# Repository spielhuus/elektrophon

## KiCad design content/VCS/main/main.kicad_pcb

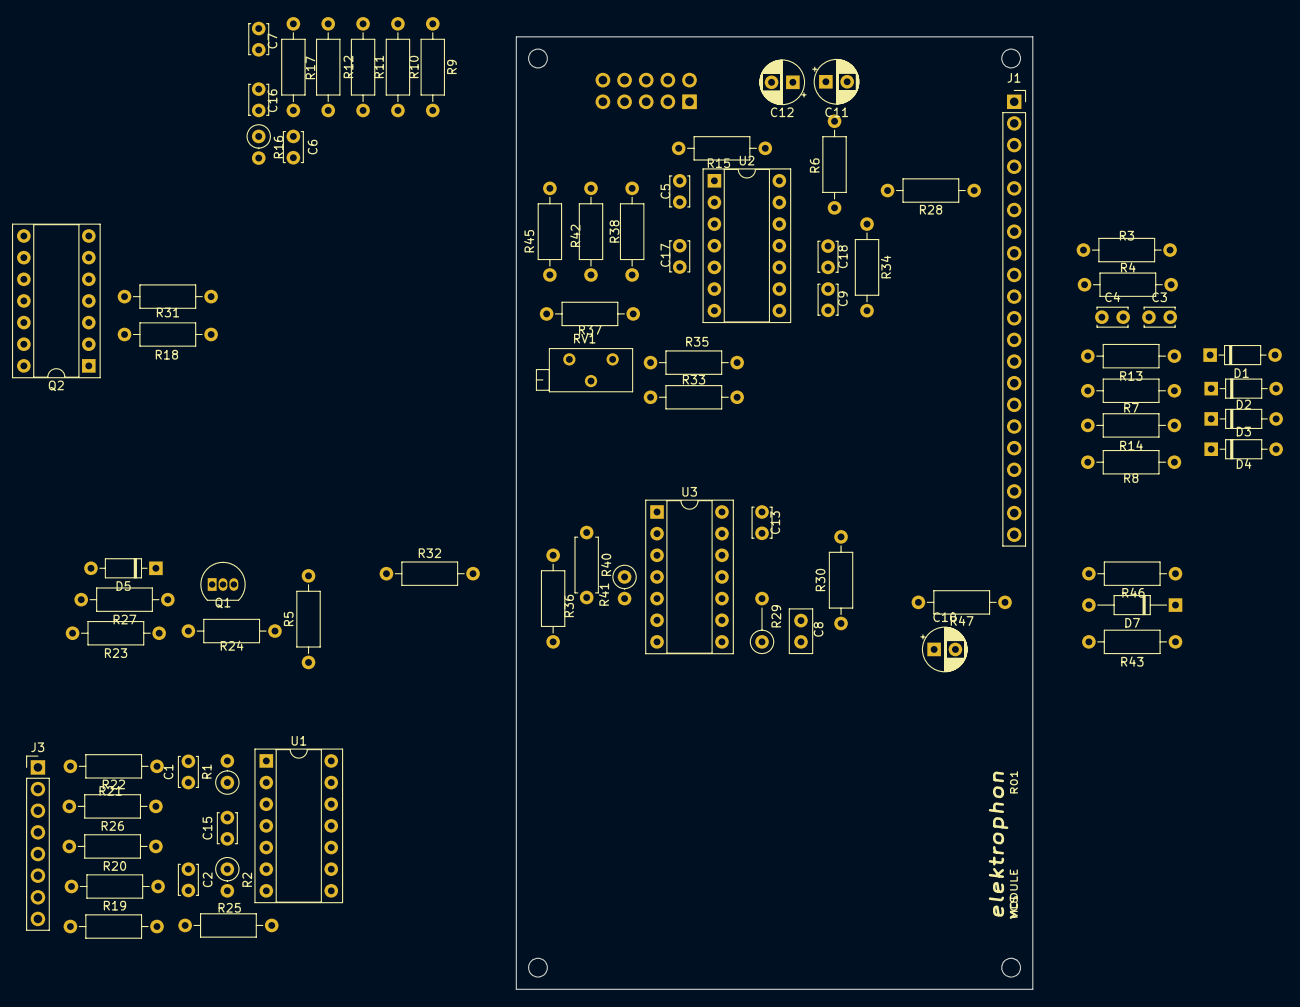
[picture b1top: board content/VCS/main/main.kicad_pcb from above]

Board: 2 copper layers, 60.6 x 111.8 mm, 81 parts (1 on the bottom side), 55 nets, no tracks yet.

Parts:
C1, C2, C5, C6, C7: 47p; C_Disc_D3.4mm_W2.1mm_P2.50mm
C3, C4: 1n; C_Disc_D3.4mm_W2.1mm_P2.50mm
C8: 47p; C_Disc_D5.0mm_W2.5mm_P2.50mm
C9: 22n; C_Disc_D3.4mm_W2.1mm_P2.50mm
C10: 47u; CP_Radial_D5.0mm_P2.50mm
C11, C12: 10u; CP_Radial_D5.0mm_P2.50mm
C13, C15, C16, C17, C18: 0.1u; C_Disc_D3.4mm_W2.1mm_P2.50mm
D1, D2, D3, D4, D5: 1N4148; D_DO-35_SOD27_P7.62mm_Horizontal
D7: 5v5; D_DO-35_SOD27_P10.16mm_Horizontal
H1, H2, H3, H4: MountingHole; MountingHole_2.2mm_M2
J1: Conn_01x21_Female; PinSocket_1x21_P2.54mm_Vertical
J2: IDC Header; IDC-Header_2x05_P2.54mm_Vertical
J3: Conn_01x08_Female; PinHeader_1x08_P2.54mm_Vertical
Q1: 2N3906; TO-92_Inline
Q2: THAT340; DIP-14_W7.62mm_Socket
R1, R2: 100k; R_Axial_DIN0207_L6.3mm_D2.5mm_P2.54mm_Vertical
R3, R4, R5, R6, R7, R8, R37, R42: 100k; R_Axial_DIN0207_L6.3mm_D2.5mm_P10.16mm_Horizontal
R9, R11, R47: 1M; R_Axial_DIN0207_L6.3mm_D2.5mm_P10.16mm_Horizontal
R10, R12: 470k; R_Axial_DIN0207_L6.3mm_D2.5mm_P10.16mm_Horizontal
R13, R14: 33k; R_Axial_DIN0207_L6.3mm_D2.5mm_P10.16mm_Horizontal
R15: 10M; R_Axial_DIN0207_L6.3mm_D2.5mm_P10.16mm_Horizontal
R16: 820k; R_Axial_DIN0207_L6.3mm_D2.5mm_P2.54mm_Vertical
R17, R30: 820k; R_Axial_DIN0207_L6.3mm_D2.5mm_P10.16mm_Horizontal
R18: 8k2; R_Axial_DIN0207_L6.3mm_D2.5mm_P10.16mm_Horizontal
R19, R20, R21, R22, R28: 82k; R_Axial_DIN0207_L6.3mm_D2.5mm_P10.16mm_Horizontal
R23, R27, R32, R33: 220k; R_Axial_DIN0207_L6.3mm_D2.5mm_P10.16mm_Horizontal
R24: 68k; R_Axial_DIN0207_L6.3mm_D2.5mm_P10.16mm_Horizontal
R25, R26, R43: 2k2; R_Axial_DIN0207_L6.3mm_D2.5mm_P10.16mm_Horizontal
R29: 820k; R_Axial_DIN0207_L6.3mm_D2.5mm_P5.08mm_Vertical
R31: 1k8; R_Axial_DIN0207_L6.3mm_D2.5mm_P10.16mm_Horizontal
R34: 100; R_Axial_DIN0207_L6.3mm_D2.5mm_P10.16mm_Horizontal
R35: 330k; R_Axial_DIN0207_L6.3mm_D2.5mm_P10.16mm_Horizontal
R36: 10m; R_Axial_DIN0207_L6.3mm_D2.5mm_P10.16mm_Horizontal
R38: 620k; R_Axial_DIN0207_L6.3mm_D2.5mm_P10.16mm_Horizontal
R40: 1m; R_Axial_DIN0207_L6.3mm_D2.5mm_P7.62mm_Horizontal
R41: 1m; R_Axial_DIN0207_L6.3mm_D2.5mm_P2.54mm_Vertical
R45: 330; R_Axial_DIN0207_L6.3mm_D2.5mm_P10.16mm_Horizontal
R46: 1k; R_Axial_DIN0207_L6.3mm_D2.5mm_P10.16mm_Horizontal
RV1: 100k; Potentiometer_Bourns_3296Z_Horizontal
U1, U2: TL074; DIP-14_W7.62mm_Socket
U3: LM3900; DIP-14_W7.62mm_Socket

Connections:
+5V: J2.9, J2.10
+15V: C11.1, C13.1, C13.2, C15.1, C15.2, C16.1, C17.1, C17.2, C18.1, J1.2, J2.3, J2.4, Q1.1, R24.1, R36.1, U1.4, U2.4, U3.7, U3.14
-15V: C12.2, C16.2, C18.2, J1.3, J2.1, J2.2, R27.2, U1.11, U2.11
/AC_OUT: C10.2, J1.9, R47.1
/BIPOLAR_OUT: J1.6, R42.2, R45.2
/CV: J1.5, R28.1
/CYCLE_1: C4.2, J1.11, R4.2
/CYCLE_2: D2.1, D4.1, J1.10, R46.1
/FALL: C1.1, J3.5, R1.1, U1.2
/FALL_1: C1.2, J3.4, R1.2, R10.1, U1.1
/FALL_2: J3.6, U1.10
/FALL_RATE: J3.7, R20.1
/IN: J1.4, R5.2, R6.1
/NET_1: C9.2, J1.7, R32.2, R34.1, U2.8
/OUT: C10.1, J1.8, R34.2, R35.2, R37.1, RV1.3
/RISE: C2.1, J3.8, R2.1, U1.6
/RISE_1: C2.2, J3.3, R2.2, R12.1, U1.7
/RISE_2: J3.2, U1.12
/RISE_RATE: J3.1, R22.1
/TRIGGER: C3.2, J1.12, R3.2
GND: C11.2, C12.1, D7.2, J1.1, J2.5, J2.6, J2.7, J2.8, Q2.1, Q2.4, Q2.7, Q2.11, R3.1, R4.1, R5.1, R7.1, R8.1, R9.1, R11.1, R25.2, R26.2, R31.2, R38.1, R47.2, RV1.1, U1.3, U1.5, U2.5, U2.10, U2.12, U3.1
unnamed: C3.1, R7.2, R13.1
unnamed: C4.1, R8.2, R14.1
unnamed: C5.1, R15.1
unnamed: C5.2, R6.2, U2.2
unnamed: C6.1, R9.2, R10.2, R16.1, U1.9
unnamed: C6.2, R16.2, R19.1, U1.8
unnamed: C7.1, R11.2, R12.2, R17.1, U1.13
unnamed: C7.2, R17.2, R21.1, U1.14
unnamed: C8.1, R29.1, U3.8
unnamed: C8.2, R29.2, U3.10
unnamed: C9.1, Q2.8, Q2.14, U2.9
unnamed: D1.1, D3.1, U3.13
unnamed: D1.2, D2.2, R13.2
unnamed: D3.2, D4.2, R14.2
unnamed: D5.1, Q1.3, R27.1
unnamed: D5.2, R32.1, U2.3
unnamed: D7.1, R43.1, R46.2
unnamed: Q1.2, R23.2, R24.2
unnamed: Q2.2, R21.2, R22.2, R26.1
unnamed: Q2.9, R19.2, R20.2, R25.1
unnamed: Q2.3, Q2.5, Q2.10, Q2.12, R18.2
unnamed: Q2.6, Q2.13, R28.2, R31.1
unnamed: R15.2, R18.1, U2.1
unnamed: R30.2, U3.11
unnamed: R33.1, U3.12
unnamed: R33.2, RV1.2
unnamed: R35.1, R36.2, U3.3
unnamed: R37.2, R38.2, R42.1, U2.6
unnamed: R40.1, R41.1, R43.2, U3.4
unnamed: R40.2, U3.2
unnamed: R41.2, U3.6
unnamed: R45.1, U2.7
unnamed: U2.13, U2.14
TRIG: R23.1, R30.1, U3.9

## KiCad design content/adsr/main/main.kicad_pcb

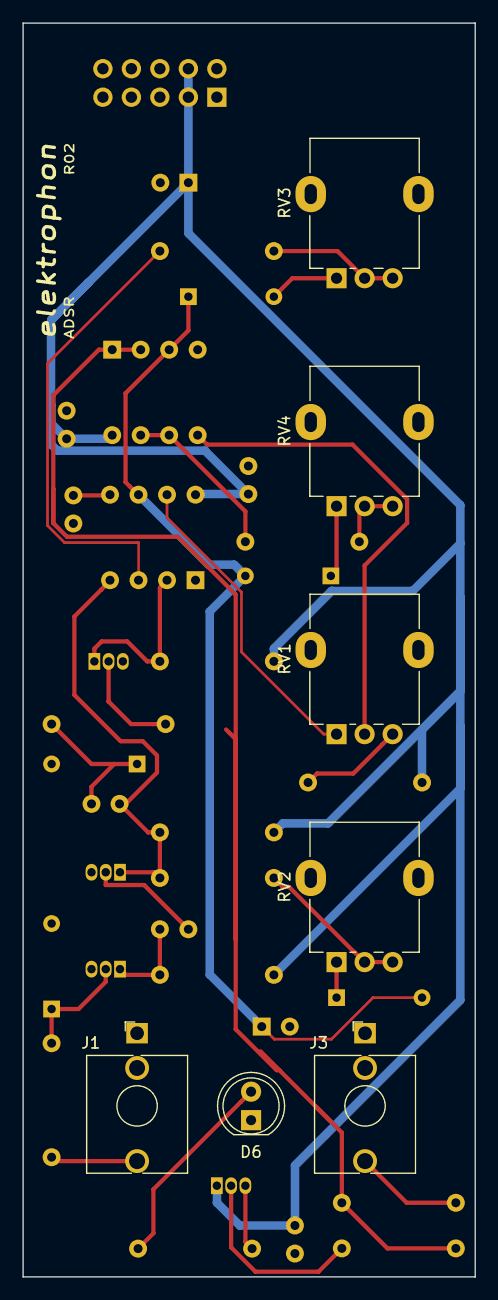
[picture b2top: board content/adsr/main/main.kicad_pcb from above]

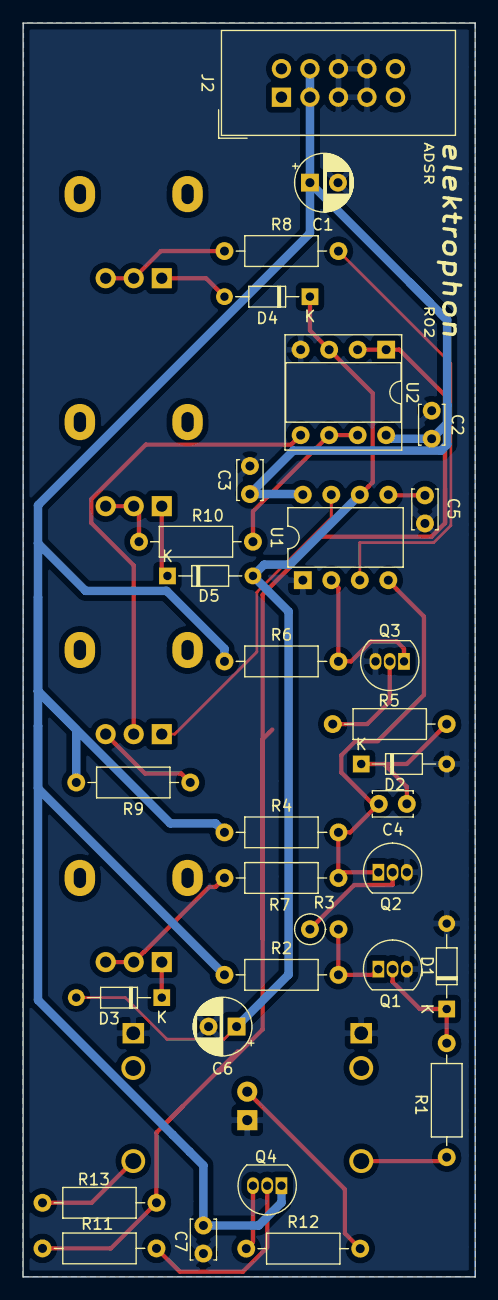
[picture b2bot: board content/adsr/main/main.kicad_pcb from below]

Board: 2 copper layers, 40.3 x 111.8 mm, 39 parts (32 on the bottom side), 28 nets.

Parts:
C1: 10u; CP_Radial_D5.0mm_P2.50mm
C2, C3: 0.1u; C_Disc_D3.4mm_W2.1mm_P2.50mm
C4, C5: 10n; C_Disc_D3.4mm_W2.1mm_P2.50mm
C6: 4u7; CP_Radial_D5.0mm_P2.50mm
C7: 100n; C_Disc_D3.4mm_W2.1mm_P2.50mm
D1, D2, D3, D4, D5: D; D_DO-34_SOD68_P7.62mm_Horizontal
D6: LED; LED_D5.0mm
J1: IN; Jack_3.5mm_QingPu_WQP-PJ398SM_Vertical_CircularHoles
J2: Power; IDC-Header_2x05_P2.54mm_Vertical
J3: OUT; Jack_3.5mm_QingPu_WQP-PJ398SM_Vertical_CircularHoles
Q1, Q2, Q3, Q4: BC547; TO-92_Inline
R1, R5, R11: 10k; R_Axial_DIN0207_L6.3mm_D2.5mm_P10.16mm_Horizontal
R2, R4, R6, R9: 4k7; R_Axial_DIN0207_L6.3mm_D2.5mm_P10.16mm_Horizontal
R3: 22k; R_Axial_DIN0207_L6.3mm_D2.5mm_P2.54mm_Vertical
R7, R8, R10: 100; R_Axial_DIN0207_L6.3mm_D2.5mm_P10.16mm_Horizontal
R12: 2k2; R_Axial_DIN0207_L6.3mm_D2.5mm_P10.16mm_Horizontal
R13: 1k; R_Axial_DIN0207_L6.3mm_D2.5mm_P10.16mm_Horizontal
RV1: 10k; Potentiometer_Alpha_RD901F-40-00D_Single_Vertical
RV2, RV3, RV4: 1M LOG; Potentiometer_Alpha_RD901F-40-00D_Single_Vertical
U1: ICM7555xP; DIP-8_W7.62mm
U2: LM358; DIP-8_W7.62mm_Socket

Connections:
+15V: C1.1, C2.2, C3.1, C7.1, J2.3, J2.4, Q4.1, R2.1, R4.1, R6.1, R9.2, U1.8, U2.8
GND: C1.2, C2.1, C3.2, C5.1, C6.2, C7.2, D1.2, D2.2, D6.1, J1.S, J2.5, J2.6, J2.7, J2.8, J3.S, Q1.3, Q2.3, Q3.3, U1.1, U2.4
unnamed: C4.1, D2.1, R5.2
unnamed: C4.2, Q2.1, R4.2, R7.2, U1.4
unnamed: C5.2, U1.5
unnamed: C6.1, D3.2, D4.1, D5.2, U1.6, U2.3
unnamed: D1.1, Q1.2, R1.1
unnamed: D3.1, RV2.1
unnamed: D4.2, RV3.1
unnamed: D5.1, RV4.1
unnamed: D6.2, R12.2
unnamed: J1.T, R1.2
unnamed: J3.T, R13.2
unnamed: Q1.1, R2.2, R3.2
unnamed: Q2.2, R3.1
unnamed: Q3.1, R6.2, U1.2
unnamed: Q3.2, R5.1
unnamed: Q4.2, R11.1
unnamed: Q4.3, R12.1
unnamed: R7.1, RV2.2, RV2.3
unnamed: R8.1, RV3.2, RV3.3
unnamed: R8.2, U1.3
unnamed: R9.1, RV1.3
unnamed: R10.1, U2.6, U2.7
unnamed: R10.2, RV4.2, RV4.3
unnamed: R11.2, R13.1, U2.1, U2.2
unnamed: RV1.1, U1.7
unnamed: RV1.2, U2.5

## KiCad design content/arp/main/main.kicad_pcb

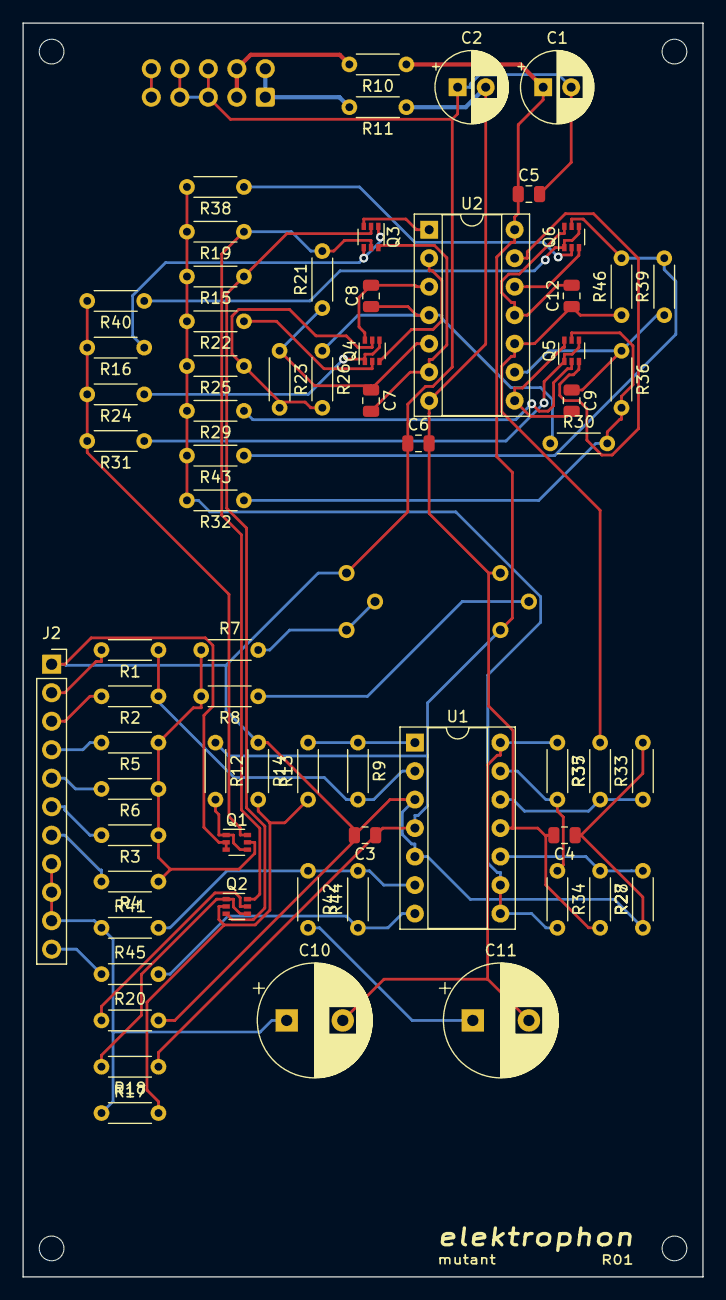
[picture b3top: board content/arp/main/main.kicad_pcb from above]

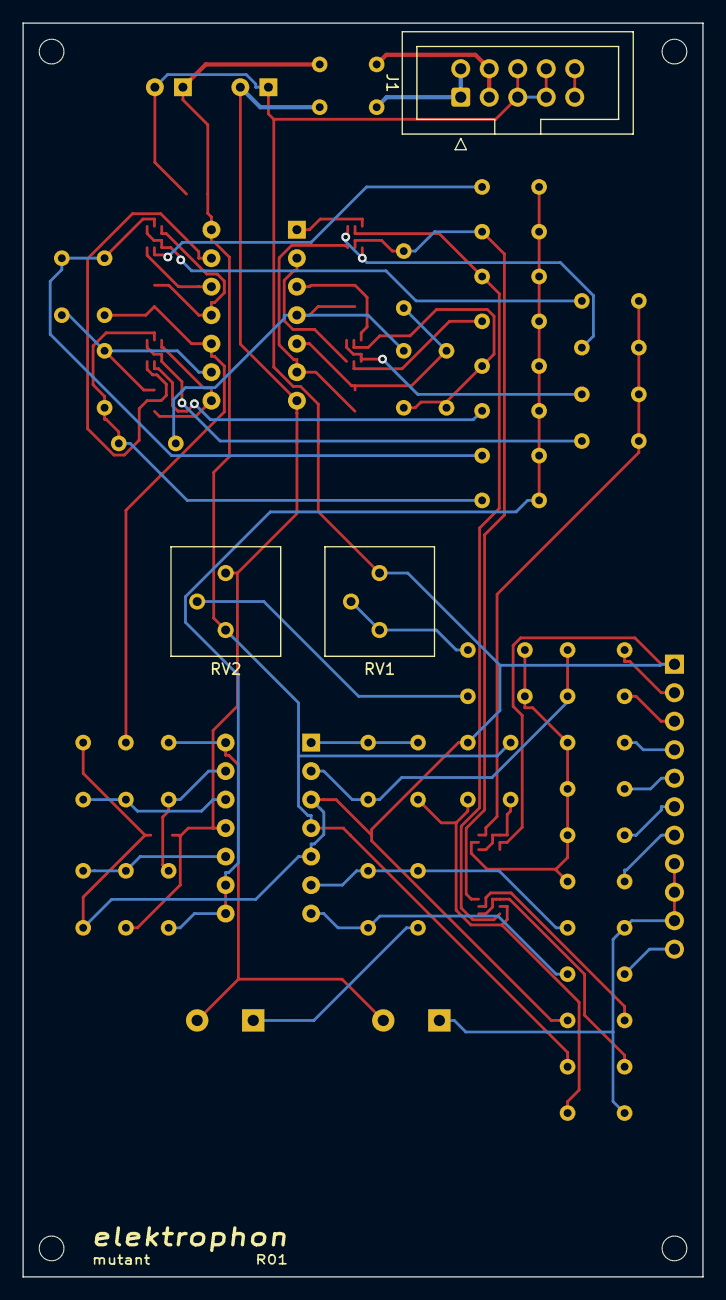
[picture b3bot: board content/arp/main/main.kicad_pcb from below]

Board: 2 copper layers, 60.6 x 111.8 mm, 74 parts (3 on the bottom side), 56 nets.

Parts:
C1, C2: 22u; CP_Radial_D6.3mm_P2.50mm
C3, C4, C5, C6: 0.1u; C_0805_2012Metric
C7, C8, C9, C12: 470p; C_0805_2012Metric
C10, C11: 22u; CP_Radial_D10.0mm_P5.00mm
J1: IDC Header; IDC-Header_2x05_P2.54mm_Vertical
J2: Conn_01x11_Female; PinSocket_1x11_P2.54mm_Vertical
Q1, Q2, Q3, Q4, Q5, Q6: MMDT3906; SOT-363_SC-70-6
R1, R2, R4, R5, R6, R8, R9, R13, R33: 100k; R_Axial_DIN0204_L3.6mm_D1.6mm_P5.08mm_Horizontal
R3: 150k; R_Axial_DIN0204_L3.6mm_D1.6mm_P5.08mm_Horizontal
R7, R14, R16, R24, R31, R40, R45: 1k; R_Axial_DIN0204_L3.6mm_D1.6mm_P5.08mm_Horizontal
R10, R11: 10; R_Axial_DIN0204_L3.6mm_D1.6mm_P5.08mm_Horizontal
R12, R21, R23, R26, R27, R28, R30, R34, R35, R36, R37, R39, R46: 10k; R_Axial_DIN0204_L3.6mm_D1.6mm_P5.08mm_Horizontal
R15, R19, R20, R22, R25, R29, R32, R38, R43: 220; R_Axial_DIN0204_L3.6mm_D1.6mm_P5.08mm_Horizontal
R17: 15k; R_Axial_DIN0204_L3.6mm_D1.6mm_P5.08mm_Horizontal
R18: 33k; R_Axial_DIN0204_L3.6mm_D1.6mm_P5.08mm_Horizontal
R41: 22k; R_Axial_DIN0204_L3.6mm_D1.6mm_P5.08mm_Horizontal
R42, R44: 56k; R_Axial_DIN0204_L3.6mm_D1.6mm_P5.08mm_Horizontal
REF1, REF2, REF3, REF4: MountingHole_2.2mm_M2
RV1: 2.2k; Potentiometer_Bourns_3386P_Vertical
RV2: 47k; Potentiometer_Bourns_3386P_Vertical
U1: TL074; DIP-14_W7.62mm_Socket
U2: LM3900; DIP-14_W7.62mm_Socket

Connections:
+5V: J1.9, J1.10
+15V: C1.1, C3.1, C5.1, R10.1, R12.1, R18.1, RV2.3, U1.4, U2.14
-15V: C2.2, C4.2, C6.2, R11.1, R28.2, RV2.1, U1.11, U2.7
CV1: J2.4, R5.2
CV2: J2.5, R6.2
FREQ: J2.6, R3.2
GND: C1.2, C2.1, C3.2, C4.1, C5.2, C6.1, J1.5, J1.6, J1.7, J1.8, J2.1, Q1.2, Q1.3, R14.1, R20.2, R27.1, R33.2, RV1.1, U1.3, U1.5
IN1: J2.2, R1.2
IN2: J2.3, R2.2
unnamed: C7.1, R21.1, R23.1, U2.5
unnamed: C7.2, Q3.6, U2.6
unnamed: C8.1, R26.1, R30.1, U2.4
unnamed: C8.2, Q4.6, U2.3
unnamed: C9.1, R36.1, R39.1, U2.9
unnamed: C9.2, Q5.6, U2.8
unnamed: C10.2, C11.2, R37.1, U1.14
unnamed: C11.1, R42.2
unnamed: C12.1, R35.2, R46.1, U2.10
unnamed: C12.2, Q6.6, U2.11
unnamed: Q1.1, Q1.4, R12.2
unnamed: Q1.5, R3.1, R4.1, R5.1, R6.1, R7.1, R8.2
unnamed: Q1.6, R16.2, R24.2, R31.2, R40.2
unnamed: Q2.1, Q2.4, R18.2
unnamed: Q2.2, R13.1, R14.2, R17.2
unnamed: Q2.3, Q3.2, R15.1
unnamed: Q2.5, R20.1
unnamed: Q2.6, Q3.5, R19.1, R21.2
unnamed: Q3.1, Q3.4, R16.1
unnamed: Q3.3, U2.1
unnamed: Q4.1, Q4.4, R24.1
unnamed: Q4.2, R22.1
unnamed: Q4.3, U2.2
unnamed: Q4.5, R23.2, R25.1, R26.2
unnamed: Q5.1, Q5.4, R31.1
unnamed: Q5.2, R29.1
unnamed: Q5.3, U2.13
unnamed: Q5.5, R30.2, R32.1, R36.2
unnamed: Q6.1, Q6.4, R40.1
unnamed: Q6.2, R38.1
unnamed: Q6.3, U2.12
unnamed: Q6.5, R39.2, R43.1, R46.2
unnamed: R1.1, R2.1, R9.2, U1.2
unnamed: R7.2, RV1.2, RV1.3
unnamed: R8.1, RV2.2
unnamed: R9.1, R13.2, U1.1
unnamed: R15.2, R19.2, R22.2, R25.2, R29.2, R32.2, R34.2, R38.2, R43.2, U1.8, U1.9
unnamed: R27.2, R28.1, U1.10
unnamed: R33.1, R35.1, U1.12
unnamed: R34.1, R37.2, U1.13
unnamed: R41.2, R42.1, R44.2, U1.6
unnamed: R44.1, R45.2, U1.7
OUT: J2.11, R45.1
RES_A: C10.1, J2.8, J2.9, J2.10, R17.1, R41.1
VN: J1.1, J1.2, R11.2
VP: J1.3, J1.4, R10.2
V_OCT: J2.7, R4.2

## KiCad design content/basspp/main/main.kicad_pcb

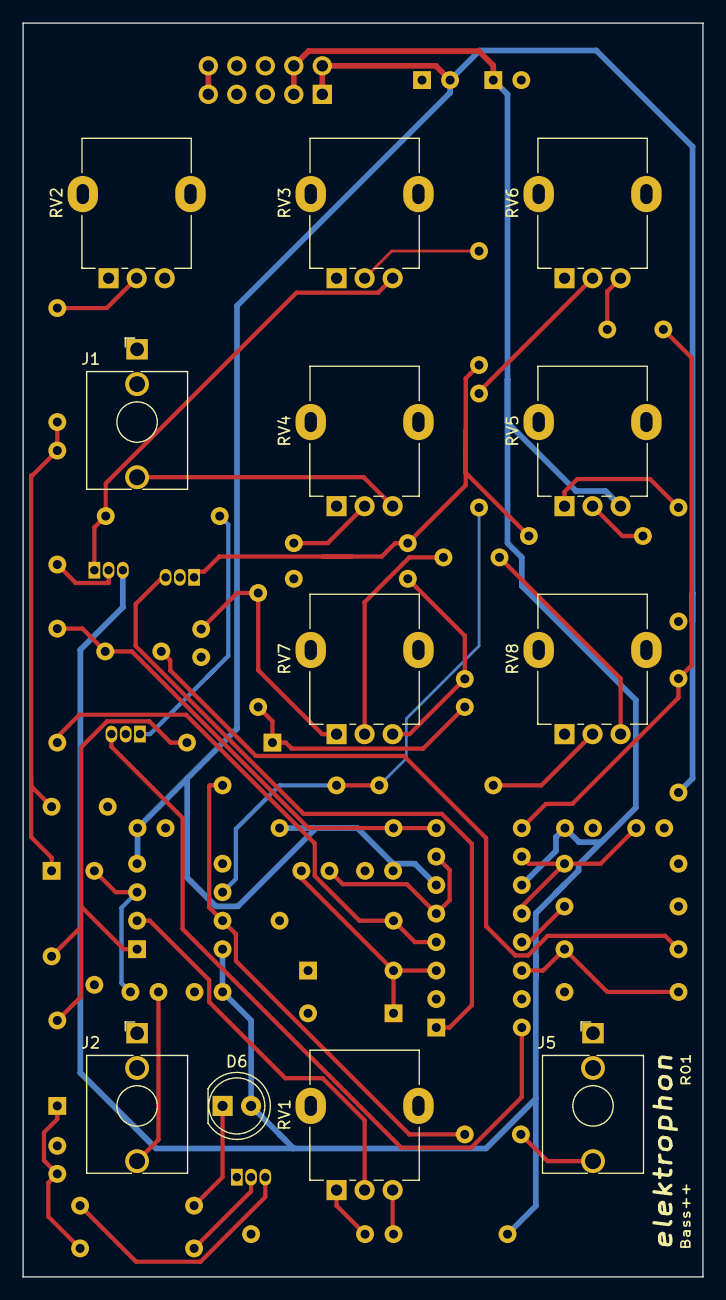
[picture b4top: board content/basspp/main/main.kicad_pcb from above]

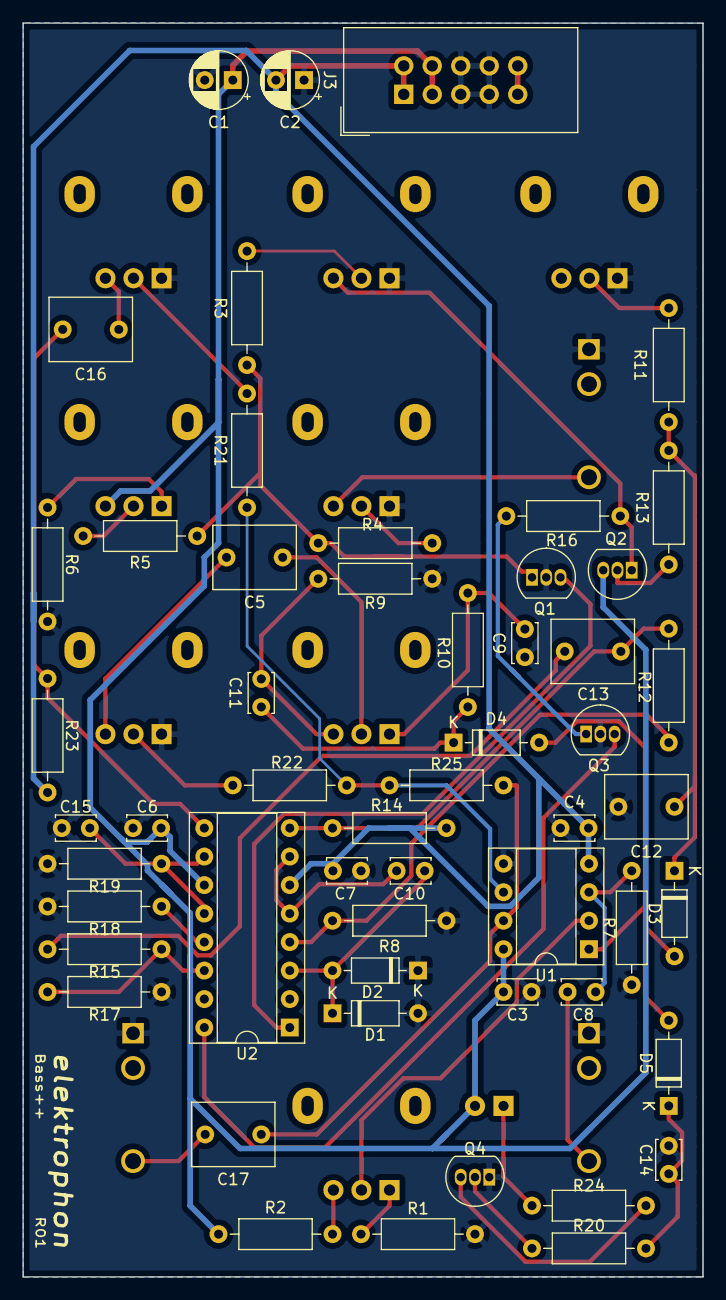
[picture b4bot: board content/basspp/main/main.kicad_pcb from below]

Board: 2 copper layers, 60.6 x 111.8 mm, 66 parts (54 on the bottom side), 47 nets.

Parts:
C1, C2: 10u; CP_Radial_D5.0mm_P2.50mm
C3, C4, C6, C7, C9, C11: 0.1u; C_Disc_D3.4mm_W2.1mm_P2.50mm
C5, C12, C13, C16, C17: 2u2; C_Rect_L7.2mm_W5.5mm_P5.00mm_FKS2_FKP2_MKS2_MKP2
C8: 1n; C_Disc_D3.4mm_W2.1mm_P2.50mm
C10, C14, C15: 10n; C_Disc_D3.4mm_W2.1mm_P2.50mm
D1, D2, D3, D4, D5: 1N4148; D_DO-35_SOD27_P7.62mm_Horizontal
D6: LED; LED_D5.0mm
J1, J5: CV; Jack_3.5mm_QingPu_WQP-PJ398SM_Vertical_CircularHoles
J2: Trigger; Jack_3.5mm_QingPu_WQP-PJ398SM_Vertical_CircularHoles
J3: IDC Header; IDC-Header_2x05_P2.54mm_Vertical
Q1, Q3: 2N3906; TO-92_Inline
Q2, Q4: 2N3904; TO-92_Inline
R1: 100; R_Axial_DIN0207_L6.3mm_D2.5mm_P10.16mm_Horizontal
R2, R12, R16: 20k; R_Axial_DIN0207_L6.3mm_D2.5mm_P10.16mm_Horizontal
R3, R15, R21, R22, R25: 100k; R_Axial_DIN0207_L6.3mm_D2.5mm_P10.16mm_Horizontal
R4, R19: 56k; R_Axial_DIN0207_L6.3mm_D2.5mm_P10.16mm_Horizontal
R5: 27k; R_Axial_DIN0207_L6.3mm_D2.5mm_P10.16mm_Horizontal
R6: 3k3; R_Axial_DIN0207_L6.3mm_D2.5mm_P10.16mm_Horizontal
R7: 1M; R_Axial_DIN0207_L6.3mm_D2.5mm_P10.16mm_Horizontal
R8, R9: 2k; R_Axial_DIN0207_L6.3mm_D2.5mm_P10.16mm_Horizontal
R10, R13, R23: 10k; R_Axial_DIN0207_L6.3mm_D2.5mm_P10.16mm_Horizontal
R11: 1k; R_Axial_DIN0207_L6.3mm_D2.5mm_P10.16mm_Horizontal
R14: 5k1; R_Axial_DIN0207_L6.3mm_D2.5mm_P10.16mm_Horizontal
R17, R18: 220; R_Axial_DIN0207_L6.3mm_D2.5mm_P10.16mm_Horizontal
R20: 220k; R_Axial_DIN0207_L6.3mm_D2.5mm_P10.16mm_Horizontal
R24: 1.5k; R_Axial_DIN0207_L6.3mm_D2.5mm_P10.16mm_Horizontal
RV1, RV3, RV7: 10k; Potentiometer_Alpha_RD901F-40-00D_Single_Vertical
RV2: 500k; Potentiometer_Alpha_RD901F-40-00D_Single_Vertical
RV4, RV5, RV6, RV8: 100k; Potentiometer_Alpha_RD901F-40-00D_Single_Vertical
U1: TL072; DIP-8_W7.62mm_Socket
U2: LM13700; DIP-16_W7.62mm_Socket

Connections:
+5V: J3.9, J3.10
+15V: C1.1, C3.1, C6.1, D6.2, J3.3, J3.4, Q2.3, R2.1, RV5.3, U1.8, U2.11
-15V: C2.2, C4.2, C7.2, J3.1, J3.2, R14.1, R23.1, U1.4, U2.6
/PULSE: D3.2, D4.2, D5.2, U1.1
/Shell: C16.1, RV6.3
GND: C1.2, C2.1, C3.2, C4.1, C6.2, C7.1, C9.1, C12.2, C14.2, C15.1, D1.1, D2.2, J1.S, J2.S, J3.5, J3.6, J3.7, J3.8, J5.S, Q1.2, Q3.2, Q4.1, R1.1, R6.1, R7.1, R8.2, R9.1, R17.1, R18.1, R19.1, RV2.1, RV3.1, RV4.1, RV6.1, RV8.1, U1.5
unnamed: C5.1, RV7.2
unnamed: C5.2, RV8.3
unnamed: C8.1, J2.T
unnamed: C8.2, R7.2, U1.3
unnamed: C9.2, R10.1, RV7.1
unnamed: C10.1, U2.5, U2.7
unnamed: C10.2, D1.2, D2.1, U2.3
unnamed: C11.1, D4.1, R10.2
unnamed: C11.2, R9.2, RV7.3
unnamed: C12.1, D3.1, R11.2, R13.2
unnamed: C13.1, R15.1
unnamed: C13.2, R12.1, R14.2, U2.8
unnamed: C14.1, D5.1, R20.2
unnamed: C15.2, R19.2, U2.10, U2.12
unnamed: C16.2, R23.2, U2.9
unnamed: C17.1, R25.1, U1.7
unnamed: C17.2, J5.T
unnamed: D6.1, R24.1
unnamed: J1.T, RV4.3
unnamed: Q1.1, R3.1, R4.1, R5.1
unnamed: Q1.3, U2.1
unnamed: Q2.1, R16.2, RV3.3
unnamed: Q2.2, R13.1
unnamed: Q3.1, R16.1
unnamed: Q3.3, U2.16
unnamed: Q4.2, R20.1
unnamed: Q4.3, R24.2
unnamed: R1.2, RV1.1
unnamed: R2.2, RV1.3
unnamed: R3.2, RV3.2
unnamed: R4.2, RV4.2
unnamed: R5.2, RV5.2
unnamed: R6.2, RV5.1
unnamed: R11.1, RV2.2
unnamed: R8.1, R12.2, U2.4
unnamed: R15.2, R17.2, U2.14
unnamed: R18.2, U2.13
unnamed: R21.1, R22.1, R25.2, U1.6
unnamed: R21.2, RV6.2
unnamed: R22.2, RV8.2
unnamed: RV1.2, U1.2

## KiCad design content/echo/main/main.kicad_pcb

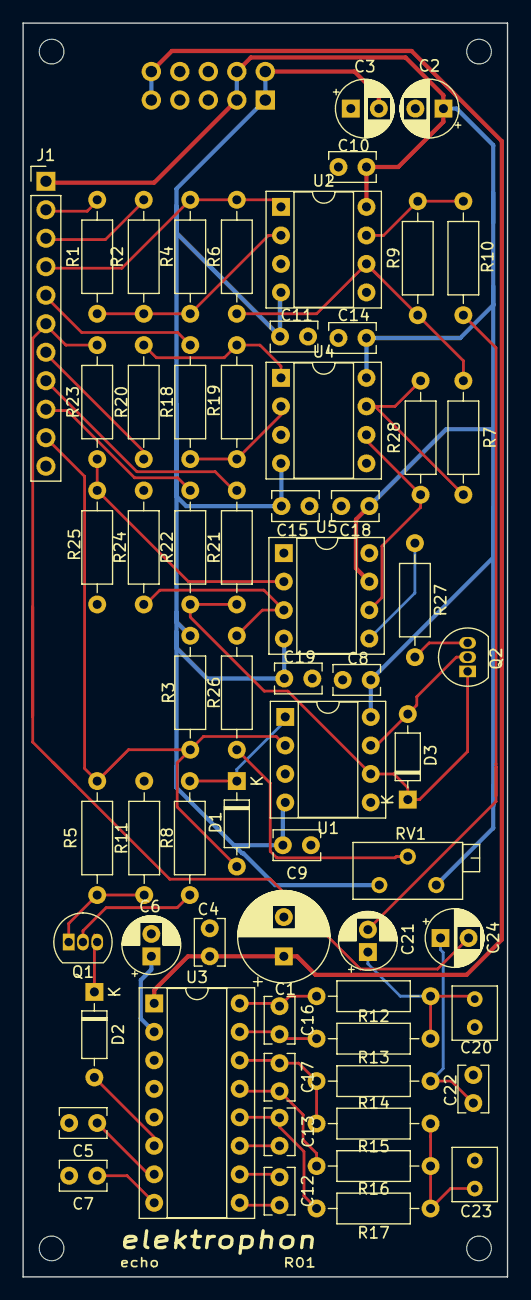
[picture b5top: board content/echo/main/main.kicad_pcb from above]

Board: 2 copper layers, 43.2 x 111.8 mm, 69 parts (1 on the bottom side), 47 nets.

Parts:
C1: 100u; CP_Radial_D8.0mm_P3.50mm
C2, C3, C24: 10u; CP_Radial_D5.0mm_P2.50mm
C4, C5, C7, C8, C9, C10, C11, C12, C13, C14, C15, C18, C19: 0.1u; C_Rect_L4.0mm_W2.5mm_P2.50mm
C6, C21: 4.7u; CP_Radial_D5.0mm_P2.00mm
C16, C17: 560p; C_Rect_L4.0mm_W2.5mm_P2.50mm
C20, C23: 5n6; C_Rect_L4.6mm_W3.8mm_P2.50mm_MKS02_FKP02
C22: 10n; C_Rect_L4.0mm_W2.5mm_P2.50mm
D1, D2, D3: 1N4148; D_DO-35_SOD27_P7.62mm_Horizontal
H1, H2, H3, H4: MountingHole; MountingHole_2.2mm_M2
J1: Conn_01x11_Female; PinHeader_1x11_P2.54mm_Vertical
J2: IDC Header; IDC-Header_2x05_P2.54mm_Vertical
Q1: 2N3904; TO-92_Inline
Q2: 2N3906; TO-92_Inline
R1, R2, R4, R6, R7, R9, R18, R19, R23: 100k; R_Axial_DIN0207_L6.3mm_D2.5mm_P10.16mm_Horizontal
R3: 300k; R_Axial_DIN0207_L6.3mm_D2.5mm_P10.16mm_Horizontal
R5, R27: 27k; R_Axial_DIN0207_L6.3mm_D2.5mm_P10.16mm_Horizontal
R8: 220k; R_Axial_DIN0207_L6.3mm_D2.5mm_P10.16mm_Horizontal
R10, R13, R15, R17: 15k; R_Axial_DIN0207_L6.3mm_D2.5mm_P10.16mm_Horizontal
R11, R24, R25: 470; R_Axial_DIN0207_L6.3mm_D2.5mm_P10.16mm_Horizontal
R12, R16: 10k; R_Axial_DIN0207_L6.3mm_D2.5mm_P10.16mm_Horizontal
R14: 2k7; R_Axial_DIN0207_L6.3mm_D2.5mm_P10.16mm_Horizontal
R20: 1k; R_Axial_DIN0207_L6.3mm_D2.5mm_P10.16mm_Horizontal
R21: 20k; R_Axial_DIN0207_L6.3mm_D2.5mm_P10.16mm_Horizontal
R22, R28: 47k; R_Axial_DIN0207_L6.3mm_D2.5mm_P10.16mm_Horizontal
R26: 1M; R_Axial_DIN0207_L6.3mm_D2.5mm_P10.16mm_Horizontal
RV1: 100k; Potentiometer_Bourns_3296Z_Horizontal
U1: TL072; DIP-8_W7.62mm_Socket
U2, U4: OPA2134; DIP-8_W7.62mm_Socket
U3: PT2399; DIP-16_W7.62mm_Socket
U5: CA3080; DIP-8_W7.62mm_Socket

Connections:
+5V: C1.1, C4.1, J2.9, J2.10, U3.1
+15V: C2.1, C8.1, C10.1, C14.1, C18.1, J1.1, J2.3, J2.4, RV1.3, U1.8, U2.8, U4.8, U5.7
-15V: C3.2, C9.2, C11.2, C15.2, C19.2, J2.1, J2.2, R3.1, RV1.1, U1.4, U2.4, U4.4, U5.4
/CV: D1.2, J1.10, R3.2, R5.2, U1.2
/IN1: J1.2, R1.2
/IN2: J1.3, R2.2
/MIXED_OUT: J1.7, R20.1
/MIX_1: J1.4, R4.1, R6.2, U2.1
/MIX_2: J1.5, R18.2
/MIX_3: C24.2, J1.6, R23.2
/RECIRC: R7.2, R28.2, U4.7
/RECIRC_ATTEN: J1.9, R22.2
/RECIRC_IN: J1.8, R21.2
/VCO: D2.2, U3.6
GND: C1.2, C2.2, C3.1, C4.2, C5.2, C6.2, C7.2, C8.2, C9.1, C10.2, C11.1, C14.2, C15.1, C18.2, C19.1, C20.2, C22.2, C23.2, J1.11, J2.5, J2.6, J2.7, J2.8, R11.1, R24.2, R25.2, U1.3, U1.5, U2.3, U2.5, U3.3, U3.4, U4.3, U4.5
unnamed: C5.1, U3.7
unnamed: C6.1, U3.2
unnamed: C7.1, U3.8
unnamed: C12.1, U3.10
unnamed: C12.2, U3.9
unnamed: C13.1, U3.11
unnamed: C13.2, R17.2, U3.12
unnamed: C16.1, R12.2, U3.16
unnamed: C16.2, R13.2, U3.15
unnamed: C17.1, R14.2, R15.2, U3.14
unnamed: C17.2, R16.2, U3.13
unnamed: C20.1, C21.1, R12.1, R13.1
unnamed: C21.2, R10.1
unnamed: C22.1, C24.1, R14.1
unnamed: C23.1, R15.1, R16.1, R17.1
unnamed: D1.1, R8.2, U1.1
unnamed: D2.1, Q1.3
unnamed: D3.1, Q2.1, R21.1, R22.1, U1.6
unnamed: D3.2, Q2.2, U1.7
unnamed: Q1.1, R5.1, R11.2
unnamed: Q1.2, R8.1
unnamed: Q2.3, R27.1
unnamed: R1.1, R2.1, R4.2, U2.2
unnamed: R6.1, R7.1, R9.2, U2.6
unnamed: R9.1, R10.2, U2.7
unnamed: R18.1, R19.2, U4.2
unnamed: R19.1, R20.2, U4.1
unnamed: R23.1, R25.1, U5.2
unnamed: R24.1, R26.2, U5.3
unnamed: R26.1, RV1.2
unnamed: R27.2, U5.5
unnamed: R28.1, U4.6, U5.6

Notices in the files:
content/VCS/main/main.kicad_pcb:
License CC BY 4.0 - Attribution 4.0 International
